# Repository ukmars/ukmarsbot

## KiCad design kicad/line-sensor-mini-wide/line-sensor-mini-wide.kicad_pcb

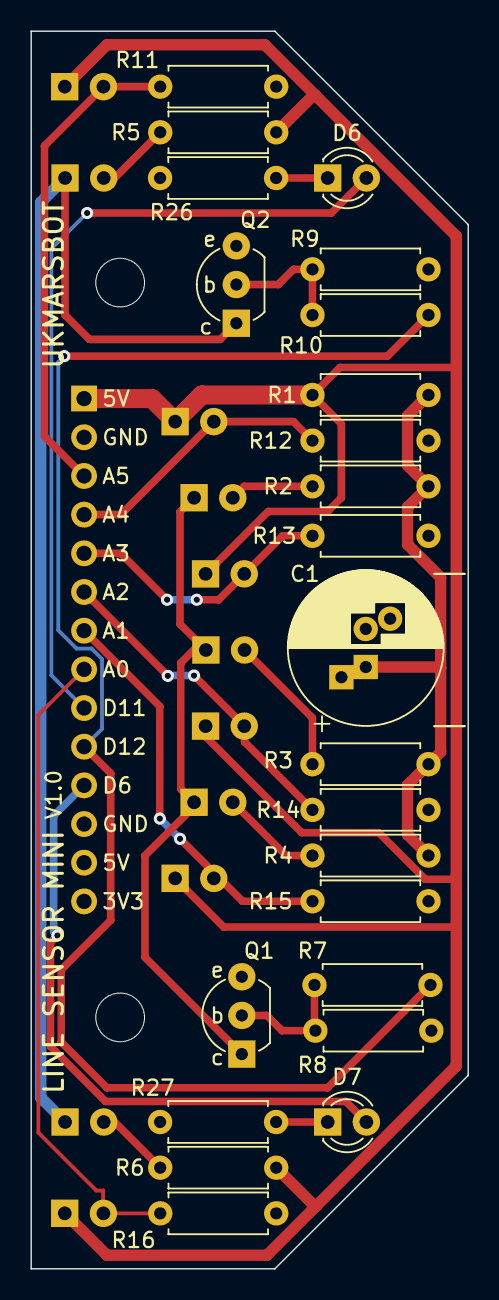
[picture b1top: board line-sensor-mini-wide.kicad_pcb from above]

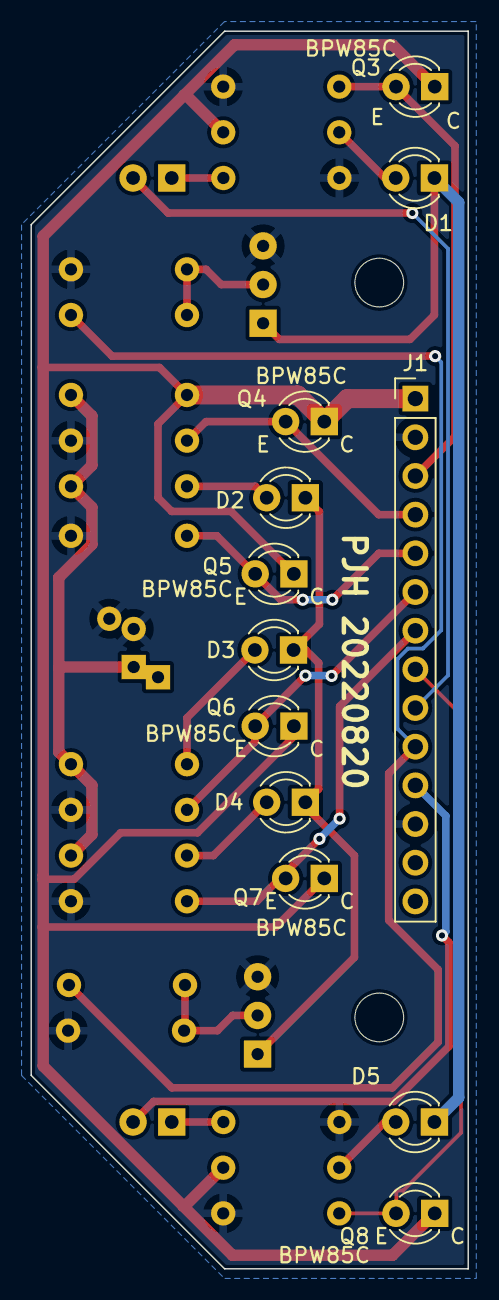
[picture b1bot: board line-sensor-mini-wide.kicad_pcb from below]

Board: 2 copper layers, 28.7 x 81.3 mm, 37 parts (12 on the bottom side), 23 nets.

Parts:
C1: 470uF; CP_Radial_D10.0mm_P2.50mm_P5.00mm
D1, D2, D3, D4, D5, D6, D7: LED; LED_D3.0mm
H1, H2: MountingHole; MountingHole_3.2mm_M3
J1: SENSORS; PinHeader_1x14_P2.54mm_Vertical
Q1, Q2: BC337; TO-92_Inline_Wide_HandSolder
Q3, Q4, Q5, Q6, Q7, Q8: BPW85C; Phototransistor_3mm_Vertical_Clear
R1: 33R; R_Axial_DIN0207_L6.3mm_D2.5mm_P7.62mm_Horizontal
R2, R3, R4, R5, R6: 68R; R_Axial_DIN0207_L6.3mm_D2.5mm_P7.62mm_Horizontal
R7, R9: 390; R_Axial_DIN0207_L6.3mm_D2.5mm_P7.62mm_Horizontal
R8, R10: 10k; R_Axial_DIN0207_L6.3mm_D2.5mm_P7.62mm_Horizontal
R11, R12, R13, R14, R15, R16, R26, R27: 2k0; R_Axial_DIN0207_L6.3mm_D2.5mm_P7.62mm_Horizontal

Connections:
5V: J1.1, Q3.1 (C), Q4.1 (C), Q5.1 (C), Q6.1 (C), Q7.1 (C), Q8.1 (C), R1.2, R5.2, R6.1
/5V_EMITTERS: C1.1, R1.1, R2.2, R3.1, R4.2
/marker_emitters: D1.1 (K), D5.1 (K), Q2.1 (C)
/sensor_emitters: D2.1 (K), D3.1 (K), D4.1 (K), Q1.1 (C)
A0_START_MARKER: J1.8, Q8.2 (E), R16.1
A1_LINE_1: J1.7, Q7.2 (E), R15.1
A2_LINE_2: J1.6, Q6.2 (E), R14.1
A3_LINE_3: J1.5, Q5.2 (E), R13.1
A4_LINE_4: J1.4, Q4.2 (E), R12.1
A5_LEFT_MARKER: J1.3, Q3.2 (E), R11.1
D6_LED_RIGHT: D7.2 (A), J1.11
D11_LED_LEFT: D6.2 (A), J1.9
D12_EMITTERS: J1.10, R7.1, R9.1
GND: C1.2, J1.2, J1.12, Q1.3 (E), Q2.3 (E), R8.2, R10.2, R11.2, R12.2, R13.2, R14.2, R15.2, R16.2, R26.2, R27.2
unnamed: D1.2 (A), R5.1
unnamed: D2.2 (A), R2.1
unnamed: D3.2 (A), R3.2
unnamed: D4.2 (A), R4.1
unnamed: D5.2 (A), R6.2
unnamed: D6.1 (K), R26.1
unnamed: D7.1 (K), R27.1
unnamed: Q1.2 (B), R7.2, R8.1
unnamed: Q2.2 (B), R9.2, R10.1
